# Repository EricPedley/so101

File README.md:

# SO-101

This is a toy project to practice my robotics skills. The goal is to, in 24 hours, train a robot arm policy with the SO-101 robot arm in simulation in Isaac Gym, then deploy the policy in Gazebo. The goal will be to have the arm stack two cubes, given only the camera feed and joint angles

# Testing isaac sim control
1. isaac_py /so101_moveit_control/launch/isaac_moveit.py`
2. ros2 run joint_state_publisher_gui joint_state_publisher_gui
3. (new terminal) ros2 topic pub /robot_description std_msgs/msg/String "data: '$(cat /home/miller/code/so101/models/SO101/so101_new_calib.urdf)'" --once

4. ros2 run topic_tools relay /joint_states /joint_command

# Ros workspace installation
I so101_moveit_control and models/SO101 symlinked in to my ros workspace. This is what it looks like:
```
~/code/so101/ros_ws
> ls -l src
total 44
drwxrwxr-x 17 miller miller 4096 Jul 30 21:55 build
drwxrwxr-x 16 miller miller 4096 Jul 30 21:55 install
drwxrwxr-x  8 miller miller 4096 Jul 30 21:04 launch_param_builder
drwxrwxr-x  3 miller miller 4096 Jul 30 21:55 log
drwxrwxr-x 18 miller miller 4096 Jul 30 21:21 moveit2
drwxrwxr-x  9 miller miller 4096 Jul 31 12:04 moveit2_tutorials
drwxrwxr-x 10 miller miller 4096 Jul 30 21:04 moveit_resources
drwxrwxr-x 10 miller miller 4096 Jul 30 21:04 moveit_task_constructor
drwxrwxr-x  8 miller miller 4096 Jul 30 21:05 moveit_visual_tools
drwxrwxr-x  9 miller miller 4096 Jul 30 21:04 rosparam_shortcuts
lrwxrwxrwx  1 miller miller   19 Aug  1 21:22 so101_description -> ../../models/SO101/
lrwxrwxrwx  1 miller miller   27 Jul 31 11:41 so101_moveit_control -> ../../so101_moveit_control/
drwxrwxr-x  9 miller miller 4096 Jul 30 21:04 srdfdom
```

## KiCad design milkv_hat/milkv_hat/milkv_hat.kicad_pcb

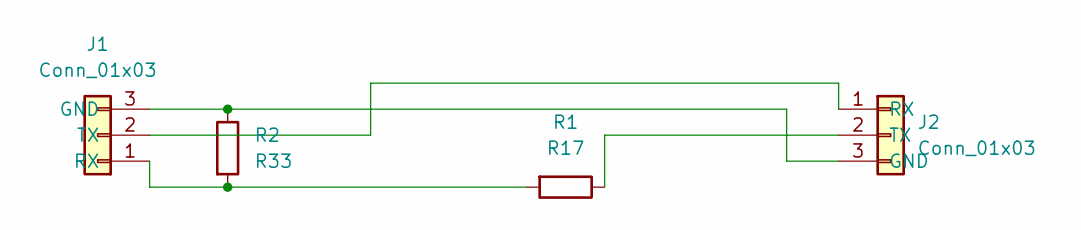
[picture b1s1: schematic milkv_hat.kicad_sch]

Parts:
J1: Conn_01x03; PinSocket_1x03_P2.54mm_Horizontal
J2: Conn_01x03; PinSocket_1x03_P2.54mm_Vertical
R1: R17; R_Axial_DIN0207_L6.3mm_D2.5mm_P10.16mm_Horizontal
R2: R33; R_Axial_DIN0207_L6.3mm_D2.5mm_P10.16mm_Horizontal

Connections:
unnamed: J1.3 (GND), J2.3 (GND), R2.1
unnamed: J1.1 (RX), R1.2, R2.2
unnamed: J1.2 (TX), J2.1 (RX)
unnamed: J2.2 (TX), R1.1

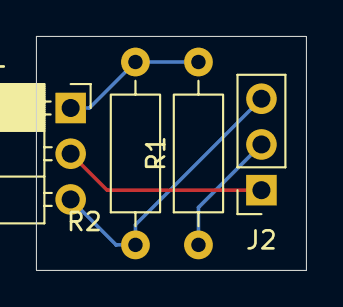
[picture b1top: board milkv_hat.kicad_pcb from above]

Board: 2 copper layers, 15.0 x 13.0 mm, 4 parts (0 on the bottom side), 4 nets.

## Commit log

2025-07-28 initial commit
    add README, gitignore, and SO101 robot model
2025-07-28 create usd file with camera
2025-07-28 create isaac script to just launch the sim
2025-07-28 get arms to spawn and twitch randomly
2025-07-28 spawning multiple arms in the environment works now
2025-07-28 get rl env to run
2025-07-28 rename file
2025-07-29 add pycache to gitignore
2025-07-29 paste in isaaclab stable baselines generic script
2025-07-29 add training outputs to gitiginore
2025-07-29 modify script to use custom env (doesnt work, just freezes)
2025-07-29 get crap to run with stable baselines wrapper
2025-07-29 make reward function use gripper position
    in theory this should train now but the loss doesn't move
2025-07-29 change reward function and number of timesteps
2025-07-29 add cubes spawning in
2025-07-29 slow down arm and spawn cubes closer to arm
2025-07-29 use limited action space and make reward function to move towards cube
2025-07-30 paste in default config from skrl
2025-07-30 replace skrl config with one from reach example
2025-07-30 reward goes up for custom reach task!
2025-07-31 add orientation reward and try turning arm collisions on
2025-07-31 add ability to load checkpoints
2025-07-31 add collider presets to gripper and jaw
2025-07-31 get running again without orientation
2025-07-31 remove camera, add more colliders
2025-07-31 modify colliders in robot usd file
2025-07-31 change grasp location to match weird frame orientation for gripper
2025-07-31 bump up training steps
2025-07-31 paste in moveit isaac sim connector tutorial script
2025-07-31 init ros2 package
2025-07-31 get ros2 control of robot arm in isaac working
2025-08-01 get roomba api to work
2025-08-02 add a bunch of config bullshit to try to get moveit trajectory planner node to launch correctly
2025-08-02 Add documentation for ros workspace
2025-08-02 fix shit so move_group node launches without crashing
2025-08-02 make script that can connect to move group action server and send an action
2025-08-04 add python files to interface with camera
2025-08-04 add launch configs for debugging orb slam
2025-08-04 update build to work :)
2025-08-07 design a pcb for the 5v to 3.3v on the roomba connector
